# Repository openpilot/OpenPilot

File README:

This branch holds utilities to maintain the git repository

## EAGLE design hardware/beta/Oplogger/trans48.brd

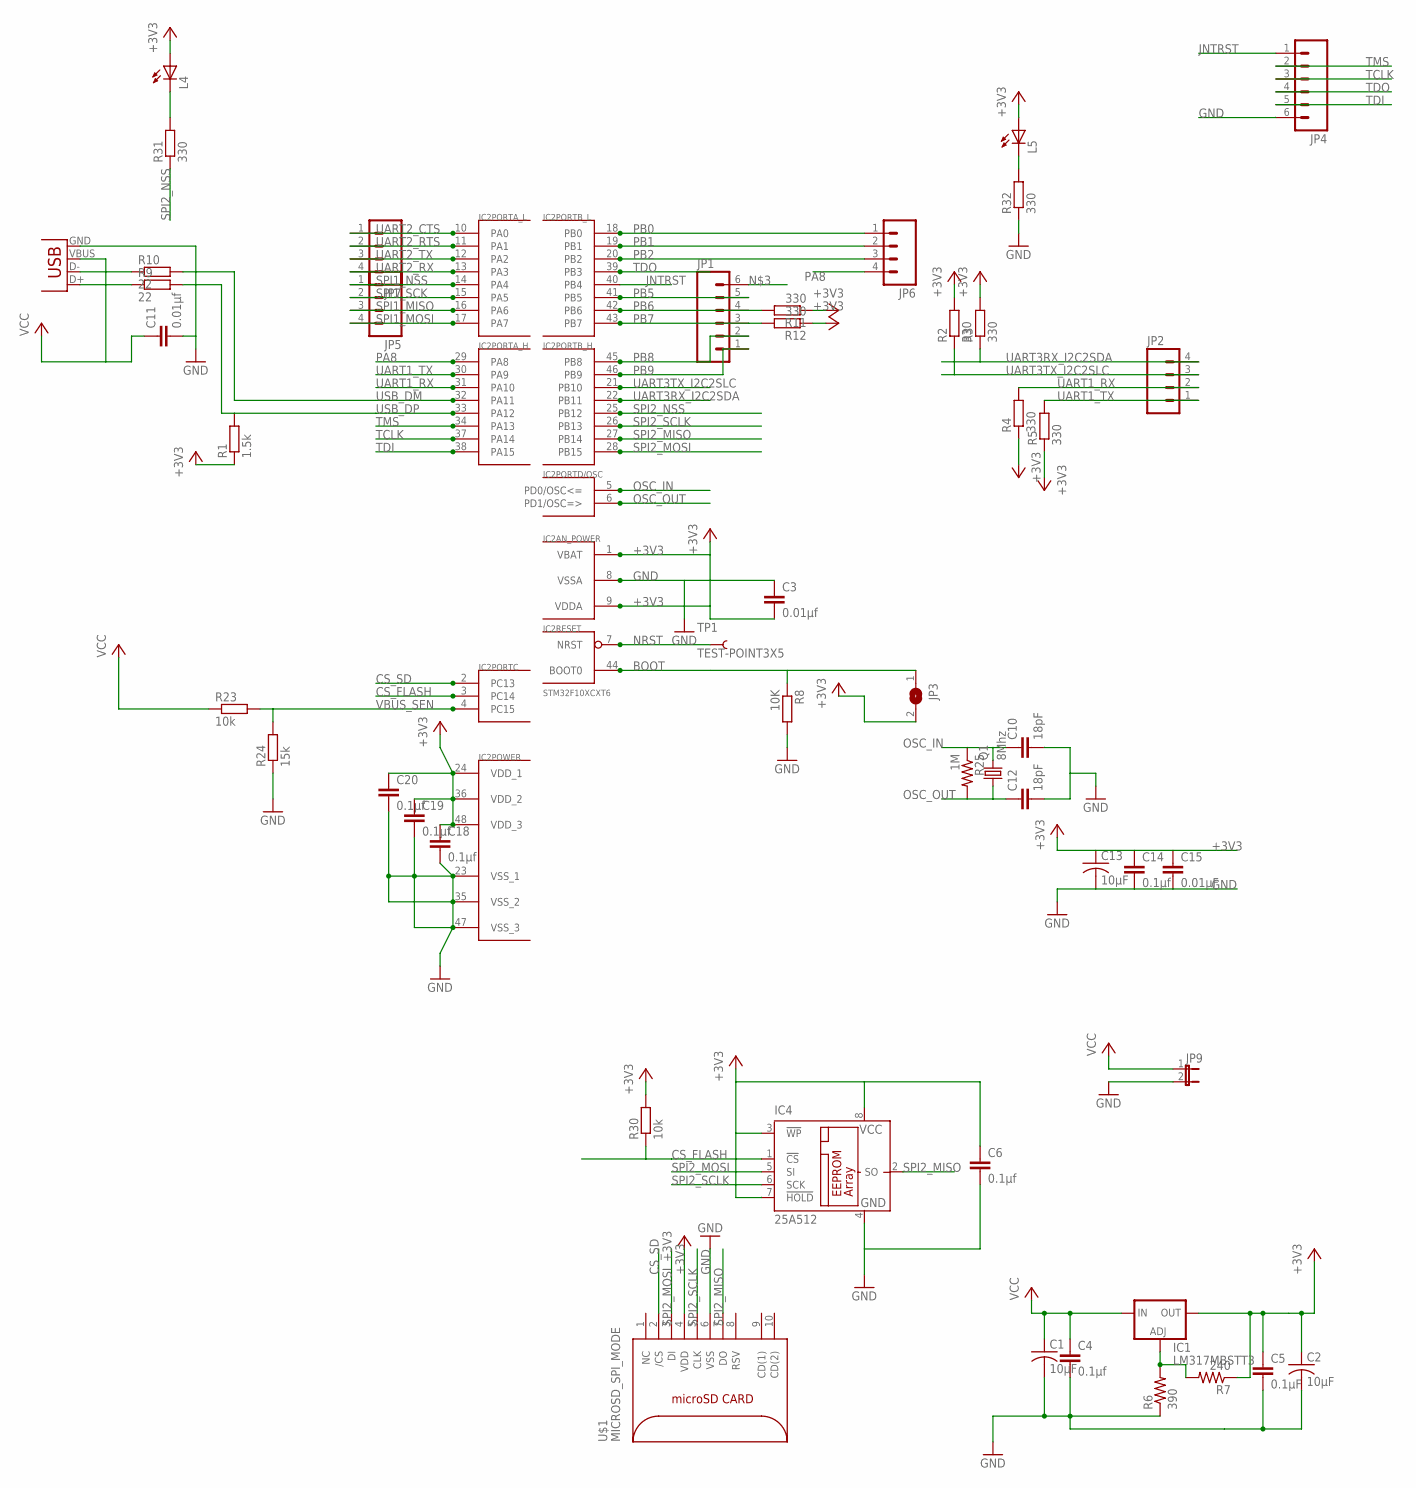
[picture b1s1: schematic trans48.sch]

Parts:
C1, C2, C13: 10µF; C1206
C3, C11: 0.01µf; C0402
C4, C6, C18, C19, C20: 0.1µf; C0402
C5: 0.1µF; C0402
C10, C12: 18pF; C0603
C14: 0.1µf; C0603
C15: 0.01µF; C0603
IC1: LM317MBSTT3; SOT223
IC2: STM32F10XCXT6; TQFP48
IC4: 25A512; SO-08
JP1, JP4: M06EM406; EM406
JP2, JP5, JP6, JP7: M04SMD2; 1X04-1MM-RA
JP3: SJ
JP9: JUMPER-2SMD-NO-NS; SJ_2S-NO-NS
L4, L5: LEDSML0603; SML0603
Q1: 8Mhz; SM49
R1: 1.5k; R0402
R2, R3, R4, R5, R11, R12, R31, R32: 330; R0402
R6: 390; R0603
R7: 240; R0603
R8: 10K; R0402
R9, R10: 22; R0402
R23, R30: 10k; R0402
R24: 15k; R0402
R25: 1M; R0603
TP1: TEST-POINT3X5; PAD.03X.05
U$1: MICROSD_SPI_MODE; MICRO_SD_CONNECTOR
X1: USB-MICROB

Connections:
+3V3: C2.1, C3.2, C5.1, C6.1, C13.1, C14.1, C15.1, C18.1, C19.1, C20.1, IC1.4 (OUT), IC2.1 (VBAT), IC2.9 (VDDA), IC2.24 (VDD_1), IC2.36 (VDD_2), IC2.48 (VDD_3), IC4.3 (!WP), IC4.7 (!HOLD), IC4.8 (VCC), JP3.2, L4.A, L5.A, R1.1, R2.2, R3.2, R4.1, R5.1, R7.1, R11.1, R12.1, R30.2, U$1.4 (VDD)
BOOT: IC2.44 (BOOT0), JP3.1, R8.1
CS_FLASH: IC2.3 (PC14), IC4.1 (!CS), R30.1
CS_SD: IC2.2 (PC13), U$1.2 (/CS)
GND: C1.2, C2.2, C3.1, C4.2, C5.2, C6.2, C10.2, C11.2, C12.2, C13.2, C14.2, C15.2, C18.2, C19.2, C20.2, IC2.8 (VSSA), IC2.23 (VSS_1), IC2.35 (VSS_2), IC2.47 (VSS_3), IC4.4 (GND), JP4.6, JP9.2, R6.1, R8.2, R24.1, R32.1, U$1.6 (VSS), X1.GND
JNTRST: IC2.40 (PB4), JP4.1
unnamed: R10.1, X1.D-
unnamed: R9.1, X1.D+
unnamed: L4.C, R31.2
unnamed: L5.C, R32.2
unnamed: IC1.1 (ADJ), R6.2, R7.2
NRST: IC2.7 (NRST), TP1.P$1
OSC_IN: C10.1, IC2.5 (PD0/OSC<=), Q1.2, R25.1
OSC_OUT: C12.1, IC2.6 (PD1/OSC=>), Q1.1, R25.2
PA8: IC2.29 (PA8), JP6.4
PB0: IC2.18 (PB0), JP6.1
PB1: IC2.19 (PB1), JP6.2
PB2: IC2.20 (PB2), JP6.3
PB5: IC2.41 (PB5), JP1.5
PB6: IC2.42 (PB6), JP1.4, R11.2
PB7: IC2.43 (PB7), JP1.3, R12.2
PB8: IC2.45 (PB8), JP1.2
PB9: IC2.46 (PB9), JP1.1
SPI1_MISO: IC2.16 (PA6), JP5.3
SPI1_MOSI: IC2.17 (PA7), JP5.4
SPI1_NSS: IC2.14 (PA4), JP5.1
SPI1_SCK: IC2.15 (PA5), JP5.2
SPI2_MISO: IC2.27 (PB14), IC4.2 (SO), U$1.7 (DO)
SPI2_MOSI: IC2.28 (PB15), IC4.5 (SI), U$1.3 (DI)
SPI2_NSS: IC2.25 (PB12), R31.1
SPI2_SCLK: IC2.26 (PB13), IC4.6 (SCK), U$1.5 (CLK)
TCLK: IC2.37 (PA14), JP4.3
TDI: IC2.38 (PA15), JP4.5
TDO: IC2.39 (PB3), JP4.4
TMS: IC2.34 (PA13), JP4.2
UART1_RX: IC2.31 (PA10), JP2.2, R4.2
UART1_TX: IC2.30 (PA9), JP2.1, R5.2
UART2_CTS: IC2.10 (PA0), JP7.1
UART2_RTS: IC2.11 (PA1), JP7.2
UART2_RX: IC2.13 (PA3), JP7.4
UART2_TX: IC2.12 (PA2), JP7.3
UART3RX_I2C2SDA: IC2.22 (PB11), JP2.4, R3.1
UART3TX_I2C2SLC: IC2.21 (PB10), JP2.3, R2.1
USB_DM: IC2.32 (PA11), R10.2
USB_DP: IC2.33 (PA12), R1.2, R9.2
VBUS_SEN: IC2.4 (PC15), R23.2, R24.2
VCC: C1.1, C4.1, C11.1, IC1.3 (IN), JP9.1, R23.1, X1.VBUS

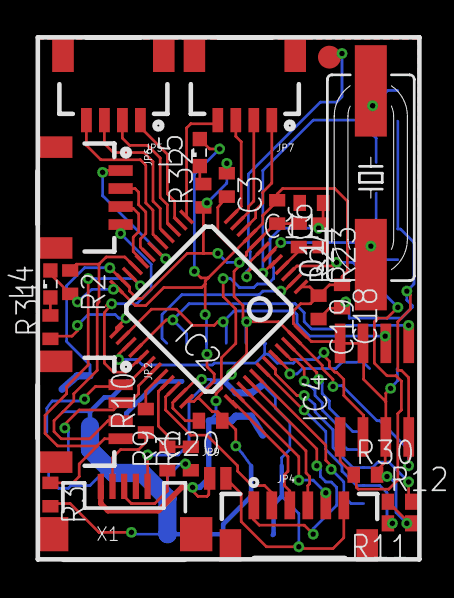
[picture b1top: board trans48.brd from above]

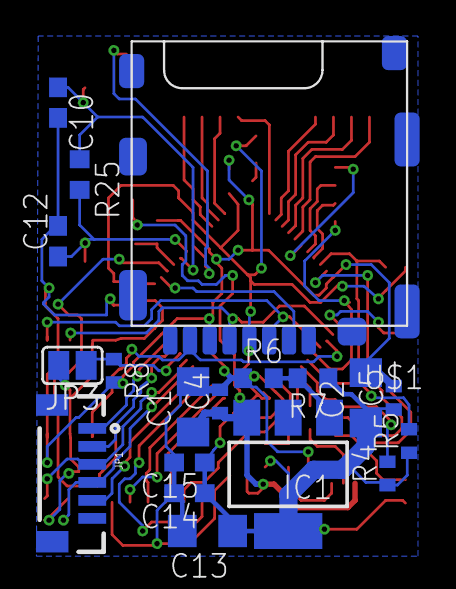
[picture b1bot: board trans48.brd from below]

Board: 2 copper layers, 50 parts (19 on the bottom side), 47 nets.

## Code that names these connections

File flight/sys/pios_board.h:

/**
 ******************************************************************************
 *
 * @file       pios_board.h   
 * @author     The OpenPilot Team, http://www.openpilot.org Copyright (C) 2009.   
 * @brief      Defines board hardware for the OpenPilot Version 0.1 hardware.
 * @see        The GNU Public License (GPL) Version 3
 *
 *****************************************************************************/
/* 
 * This program is free software; you can redistribute it and/or modify 
 * it under the terms of the GNU General Public License as published by 
 * the Free Software Foundation; either version 3 of the License, or 
 * (at your option) any later version.
 * 
 * This program is distributed in the hope that it will be useful, but 
 * WITHOUT ANY WARRANTY; without even the implied warranty of MERCHANTABILITY 
 * or FITNESS FOR A PARTICULAR PURPOSE. See the GNU General Public License 
 * for more details.
 * 
 * You should have received a copy of the GNU General Public License along 
 * with this program; if not, write to the Free Software Foundation, Inc., 
 * 59 Temple Place, Suite 330, Boston, MA 02111-1307 USA
 */


#ifndef PIOS_BOARD_H
#define PIOS_BOARD_H

//------------------------
// Default File Settings
//------------------------
#define SETTINGS_FILE			"Settings.ini"

//------------------------
// DMA Channels Used
//------------------------
/* Channel 1  - 			*/
/* Channel 2  - SPI1 (SPI_SD_RX)	*/
/* Channel 3  - SPI1 (SPI_SD_TX)	*/
/* Channel 4  - 			*/
/* Channel 5  - 			*/
/* Channel 6  - 			*/
/* Channel 7  - 			*/
/* Channel 8  - 			*/
/* Channel 9  - 			*/
/* Channel 10 - 			*/
/* Channel 11 - 			*/
/* Channel 12 - 			*/

//------------------------
// Leds Definition   
//------------------------
#define LED1_GPIO_PORT			GPIOC
#define LED1_GPIO_PIN			GPIO_Pin_12
#define LED1_GPIO_CLK			RCC_APB2Periph_GPIOC
#define LED2_GPIO_PORT			GPIOC
#define LED2_GPIO_PIN			GPIO_Pin_13
#define LED2_GPIO_CLK			RCC_APB2Periph_GPIOC
#define NUM_LED				2

//------------------------
// I2C   
//------------------------
#define I2C_GPIO_PORT			GPIOB
#define I2C_SDA_PIN			GPIO_Pin_11
#define I2C_SCL_PIN			GPIO_Pin_10

//------------------------
// Onboard Pressure sensor   
//------------------------
#define HP03D_XCLR_GPIO_PORT		GPIOC
#define HP03D_XCLR_GPIO_PIN		GPIO_Pin_15
#define HP03D_MCLK_GPIO_PORT		GPIOA
#define HP03D_MCLK_GPIO_PIN		GPIO_Pin_1

//-------------------------
// GPS UART 
//-------------------------
#define GPS_UART			USART2
#define GPS_BAUD			57600
#define GPS_GPIO_PORT			GPIOA
#define GPS_RX_PIN			GPIO_Pin_3
#define GPS_TX_PIN			GPIO_Pin_2
#define GPS_REMAP_FUNC			{ }
#define GPS_IRQ_CHANNEL			USART2_IRQn
#define GPS_IRQHANDLER_FUNC		void USART2_IRQHandler(void)
#define GPS_CLK_FUNC			RCC_APB1PeriphClockCmd(RCC_APB1Periph_USART2, ENABLE)
#define GPS_NVIC_PRIO			IRQ_PRIO_HIGHEST

//-------------------------
// Telemetry radio UART 
//-------------------------
#define TELEM_UART        		USART3
#define TELEM_BAUD         		115200
#define TELEM_GPIO_PORT         	GPIOC
#define TELEM_RX_PIN      		GPIO_Pin_11
#define TELEM_TX_PIN      		GPIO_Pin_10
#define TELEM_REMAP_FUNC		{ GPIO_PinRemapConfig(GPIO_PartialRemap_USART3, ENABLE); }
#define TELEM_IRQ_CHANNEL		USART3_IRQn
#define TELEM_IRQHANDLER_FUNC		void USART3_IRQHandler(void)
#define TELEM_CLK_FUNC			RCC_APB1PeriphClockCmd(RCC_APB1Periph_USART3, ENABLE)
#define TELEM_NVIC_PRIO			IRQ_PRIO_HIGHEST

//-------------------------
// AUXSER USART (available instead of RX5/RX6)
//-------------------------
#define AUX_UART_BAUD			19200
#define AUX_UART_UART			USART1
#define AUX_UART_GPIO_PORT		GPIOA
#define AUX_UART_RX_PIN			GPIO_Pin_10
#define AUX_UART_TX_PIN			GPIO_Pin_9
#define AUX_UART_REMAP_FUNC		{ }
#define AUX_UART_IRQ_CHANNEL		USART1_IRQn
#define AUX_UART_IRQHANDLER_FUNC	void USART1_IRQHandler(void)
#define AUX_UART_CLK_FUNC		RCC_APB2PeriphClockCmd(RCC_APB2Periph_USART1, ENABLE)
#define AUX_UART_NVIC_PRIO		IRQ_PRIO_HIGH

//-------------------------
// USART Serial Ports
//-------------------------
#define UART_NUM			3
#define UART_RX_BUFFER_SIZE		128
#define UART_TX_BUFFER_SIZE		128

//-------------------------
// Receiver PWM inputs   
//-------------------------
#define RECEIVER1_GPIO_PORT		GPIOB
#define RECEIVER1_PIN			GPIO_Pin_2      // PB2
#define RECEIVER1_TIM_PORT		TIM3
#define RECEIVER1_CH			TIM_Channel_3   // TIM3_CH3
#define RECEIVER2_GPIO_PORT		GPIOB
#define RECEIVER2_PIN			GPIO_Pin_1      // PB1
#define RECEIVER2_TIM_PORT		TIM3
#define RECEIVER2_CH			TIM_Channel_4   // TIM3_CH4
#define RECEIVER3_GPIO_PORT		GPIOA
#define RECEIVER3_PIN			GPIO_Pin_8      // PA8
#define RECEIVER3_TIM_PORT		TIM1
#define RECEIVER3_CH			TIM_Channel_1   // TIM1_CH1
#define RECEIVER4_GPIO_PORT		GPIOA
#define RECEIVER4_PIN			GPIO_Pin_0      // PA0
#define RECEIVER4_TIM_PORT		TIM5
#define RECEIVER4_CH			TIM_Channel_1   // TIM5_CH1
#define RECEIVER5_GPIO_PORT		GPIOA
#define RECEIVER5_PIN			GPIO_Pin_10     // PA10
#define RECEIVER5_TIM_PORT		TIM1
#define RECEIVER5_CH			TIM_Channel_3   // TIM1_CH3
#define RECEIVER6_GPIO_PORT		GPIOA
#define RECEIVER6_PIN			GPIO_Pin_9      // PA9
#define RECEIVER6_TIM_PORT		TIM1
#define RECEIVER6_CH			TIM_Channel_2   // TIM1_CH2

/* Not used in v0.1 HW
#define RECEIVER7_GPIO_PORT		GPIOB
#define RECEIVER7_PIN			GPIO_Pin_4      // PB4
#define RECEIVER7_TIM_PORT		TIM3
#define RECEIVER7_CH			TIM_Channel_1   // TIM3_CH1
#define RECEIVER8_GPIO_PORT		GPIOB
#define RECEIVER8_PIN			GPIO_Pin_5      // PB5
#define RECEIVER8_TIM_PORT		TIM3
#define RECEIVER8_CH			TIM_Channel_2   // TIM3_CH2
*/

#define NUM_RECEIVER_INPUTS		6

//-------------------------
// Servo outputs   
//-------------------------
#define SERVO1_4_PORT			GPIOB
#define SERVO1_PIN			GPIO_Pin_6
#define SERVO2_PIN			GPIO_Pin_7
#define SERVO3_PIN			GPIO_Pin_8
#define SERVO4_PIN			GPIO_Pin_9
#define SERVO5_8_PORT			GPIOC
#define SERVO5_PIN			GPIO_Pin_6
#define SERVO6_PIN			GPIO_Pin_7
#define SERVO7_PIN			GPIO_Pin_8
#define SERVO8_PIN			GPIO_Pin_9

#define NUM_SERVO_OUTPUTS		8

//-------------------------
// Leveler (analog inputs)
//-------------------------
#define LEVELER_GPIO_PORT		GPIOC  
#define LEVELER_Z_PIN			GPIO_Pin_0	// ADC123_IN10
#define LEVELER_A_PIN			GPIO_Pin_1	// ADC123_IN11
#define LEVELER_B_PIN			GPIO_Pin_2	// ADC123_IN12

//-------------------------  
// USB
//-------------------------
#define USB_ACC_GPIO_PORT		GPIOC
#define USB_DETECT_PIN			GPIO_Pin_4
#define USB_PULLUP_PIN			GPIO_Pin_14

//-------------------------
// Master Clock   
//-------------------------
#define MASTER_CLOCK			72000000
#define PERIPHERAL_CLOCK		(MASTER_CLOCK/2)

//-------------------------
// Interrupt Priorities
//-------------------------
#define IRQ_PRIO_LOW			12		// lower than RTOS
#define IRQ_PRIO_MID			8		// higher than RTOS
#define IRQ_PRIO_HIGH			5		// for like SPI, AIN, I2C etc...
#define IRQ_PRIO_HIGHEST		4 		// for UART etc...

#endif /* PIOS_BOARD_H */

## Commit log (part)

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2015-04-22 OP-1843 Makefile bugs: split qmake CONFIG variables as a temporary solution to broken qmake quoting on windows
2015-04-23 OP-1806 version info escape strings for C. Added option "--escape" which uses json.dumps to do escaping
2015-04-23 OP-1848 altvari0
    1. build fixes
    2. Updated ui to use updated uavo names in altitude settings that align to the naming in vtol settings
    3. Moved call the thrust altvario to pre application of PIDs for 3d axes to allow for later coupling.
2015-04-23 OP-1838 altvario
    Fixes and tidyup.
    TODO:
    1. Fix UI for sliders
    2. Disable vtol tuning on stabi input
    3. Altitude loss feedback
2015-04-23 OP-1837 Moved to Flexiport. Updated some decoding code.
2015-04-24 OP-1848 altvario
    UI scaling fixes and help text edits.
2015-04-24 OP-1837 Renaming of perf counter.
2015-04-24 OP-1855 changed , to :
2015-04-24 OP-1849 Initial commit
2015-04-25 Add Revo hardware files
2015-04-26 OP-1849 Hooks all in place for CDC line state changes to drive port GPIO for DTR
2015-04-26 Added new helper macros to performance counters.
2015-04-26 OP-1337 Translations : input wizard update
2015-04-26 OP-1849 Uncrustify
2015-04-26 OP-1837 Fixed a wrongly named config.
2015-04-27 OP-1751 Modify some improper CN translations
2015-04-27 OP-1858 autotakeoff in pathplanner
    1. Allowing arming in pathplanner
    2. Takeoff activation requires throttle to be above 30%
    3. Takeoff occurs at the current/actual position and rises vertical to the settings altititude.
    4. The details of the takeoff waypoint are effectively ignored - this is a simplicifcation to avoid having to have pathplanner inject a flyvector command from the current location to the waypoint
    5. We hard code the condition check for autotakeoff as only one mode is supported.
2015-04-27 X-Plane 10 HITL & SITL protocol changes that should have been in place long ago!
2015-04-28 OP-1858 autotakeoff and pathplanner
    1. Allow arming in pathplanner
    2. Typo in comment
2015-04-28 OP-1835 - Next Motor Constraints - Diff Addition Method
    Using the Difference / Addition method to compare it against the
    multiplication method.
2015-04-28 Fix some minor issues with the old Wireshark Plugin. It won't compile past Wireshark 1.8 which is way outdated. added void *data _U_ to the dissecor definition per - https://ask.wireshark.org/questio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
2015-04-28 Fix the error "Err Field '0' (actuatorcommand.Channel.0) is signed (FT_INT16) but is being displayed unsigned (BASE_DEC_HEX)" Stop attempting to display in hex
2015-04-28 Fix WhatsNew for release
2015-04-29 OP-1835 - Master Motor Constraints - Flow changes
2015-04-30 OP-1840 CC3D wouldn't build and update some comments
2015-04-30 resurrect missing / deleted pyuavtalk files & examples. Work with Viper to bring back up to date with current codebase.
2015-04-30 Fix the python file read example to properly read the filename from commandline. Adjusted argv accordingly in python code.
2015-05-01 Add uavobjects_python_clean function to remove the UAVOs, reduce likely hood of stale files being used.
2015-05-01 fix uavobject paths
2015-05-01 OP-1840 Remove reference to unreleased hardware
2015-05-01 OP-1870 Velocity Roam
    Auto yaw if vtolpathfollowersettings.YawControl is set to MovementDirection.
    1. Fast-forward pitch with slight roll will slowly introduce yaw continuosly, which also continuosly introduces additional banking of velocities in the NE directions, forming a circle of a large radi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
    2. Zero forward pitch, with just roll input, will trigger yaw rate quickly approaching max yaw rate, which may need to be reduced.
2015-05-01 OP-1835 - Master Motor Constraints - Bugfix
    Incorrect if/then statement
2015-05-02 OP-802 adapted gstreamer copydata.pro to use new addCopyFileTarget macro (thanks James!)
2015-05-02 OP-802 stop pipeline on error
2015-05-02 OP-802 added more plugins
2015-05-02 uncrustified
2015-05-02 OP-1835 - Motor Constraints for 15.02.02 - Quick fix to disable clipping. Bit of code not in the original fix I had to deal with.
2015-05-02 OP-1835 - Motor Constraints 15.02.02 100% throttle curves default
2015-05-03 OP-1873 - Uncrustify - Non Inverted Sbus for Flight Testing.
2015-05-03 Update WHATSNEW.txt - rel-15.02.02-RC3
2015-05-03 OP-1873 - Fix Compile Errors
2015-05-03 OP-1847 altvario update of tuning parameters for piddown control
2015-05-04 OP-1863 ratetrainer fix coding error. ratetrainer should now work.
2015-05-05 OP-187- velocityroam auto-yaw
    uncrustify
2015-05-05 OP-1848 build fixes after merge with ratetrainer
2015-05-05 OP-1848 altvario Update dT to speed on sensor update rate
2015-05-05 Be mindful of linux users not using brew on OSX... should be using sudo (not running make as root)
2015-05-06 Fix the serial connection in example.py
2015-05-06 OP-1840 another merge conflict
2015-05-06 Make changes to example python code so it makes use of StabilizationSettingsBank1 Fix some printf() errors on the tuple that held PID settings... needed one more field Fix Keyboard interrupt on one e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
2015-05-07 Don't need to request all the data first, just start read.
2015-05-07 Pull request from user aughey on github - https://github.com/openpilot/OpenPilot/pull/4/files
    Covers commits:
    This is noisy, but does talk to the CC3D - c59543a
    Don't need to request all the data first, just start read. - e4df881
    Printing RPY for testing - e3117df
2015-05-07 OP-1873 - Non Inverted S.Bus support. Based off Next.
2015-05-07 OP-1810 FOC GCS
2015-05-08 OP-1803 Disable untested DSM link quality code
2015-05-08 OP-1810 FOC re-add back in removed case statement
2015-05-08 OP-1858 takeoff in nav address code review comments
2015-05-09 OP-1848 altvario discovery4bare remove second instance of uavo
2015-05-09 Upgrade HK CCs
2015-05-09 OP-1831 - Update Ki Limits
2015-05-10 OP-1853 Ground build tidy: remove unneeded line in translations.pro
2015-05-10 OP-1810-FOC review comments
2015-05-10 Add search coloring back to the location search. Google Maps should be functional again. Some locations on the extents of map do not render 'North Pole, South Pole, Antarctica, etc.' currently a *non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
2015-05-10 OP-1810-FOCv2 undoing usb driver changes
2015-05-11 OP-1810 CC/CC3D message box : Change text and icon
2015-05-11 OP-1810 usagetracker : remove CC
2015-05-12 OP-1848 altvario fixes
    1. CC compile fix
    2. on reinit calculate a new thrustdemand after which gyro updates will retrigger subsequent calcs
2015-05-12 OP-1848 altvario gcs fix ranges
2015-05-13 OP-1810-FOC uncrustify
2015-05-13 uncrustify flight gps updates
2015-05-13 OP-1853 Ground build tidy: Remove old android line
2015-05-13 OP-1853 Ground build tidy: Make UAVO_BUILD_CONF use GCS_BUILD_CONF to match qtcreator builds and make things easier later
2015-05-13 OP-1853 Ground build tidy: removed now unneeded uavobject-synthetics.pro
2015-05-13 Fix SigPacSpainMap & Google*Korea map types
2015-05-13 OP-1869 "scale" lower case
2015-05-13 OP-1887 Hide battery links when battery panel not displayed
2015-05-14 OP-1887 Missing file for tooltips
2015-05-14 attempt to get Pergo Turkish maps working. Still buggy. Unable to search and auto zoom. Initial map render works mostly
2015-05-14 OP-1847 gps assist fixes
    1. Update vtol vertical pids
    2. Reduce deadband on throttle in gpsassist auto throttle to avoid large deviations in throttle change from neutral
    3. Reinitialise assisted control state on mode change where the flight is the same but only gpsassist is going from disabled to enabled or enabled to disabled.
2015-05-14 OP-1887 Add Receiver quality
2015-05-14 OP-1887 Oups, QuadH resurrected...
2015-05-15 OP-1337 Translations updates for rel-15.05
2015-05-15 Depreciate Yandex maps
2015-05-16 OP-1847 gpsassist fix
    Set assisted control state to HOLD when Brake controller transitions to HOLD. This impacts throttle stick behavior as it is different during braking and on brake completion in the hold state.
    Also cleanuped and removed unused/old code that triggered HOLD in plans.c
2015-05-16 OP-1882 set thrust control to auto as default
2015-05-17 Fixing indent spacing for OC reasons.
2015-05-17 adding a size output for json
2015-05-17 Add code from John Aughey - jha@aughey.com https://github.com/aughey/OpenPilot/commit/95726c7cf3f909e24c5cc5e8cd3ece56a564dff1?diff=unified
2015-05-17 add json bits to the generator
2015-05-17 OP-1892 Convert / Add descriptions
2015-05-17 change Json path to be relative to the project root. Files should be present after: make uavtalk_json; ls build/uavobject-synthetics/json
2015-05-17 add more examples to the README file. fix the serial example to be more robust
2015-05-17 OP-1893 Apply scale to reach +1/-1 range
2015-05-17 This closes https://progress.openpilot.org/browse/OP-1888
2015-05-18 OP-1892 Formatting, second round
2015-05-18 OP-1464 GPS autobaud - stash while debugging newobject issue
2015-05-19 OP-1854 Allow EKF reset with mouseclick on PFD alarm
2015-05-19 15.05 Update contributors
2015-05-20 OP-1464 remove commented out or unused code and pretty it up
2015-05-20 OP-1464 Compile warning discovery Remove AbConfStoreDisable
2015-05-21 OP-1897 Minor change after code review
2015-05-21 OP-1888: Fix SEGFAULT when deleting config.
2015-05-23 OP-1879 remove openpilot hardcoding: use same app target on all platforms
2015-05-23 OP-1879 remove openpilot hardcoding: remove udp_test from Linux install like other platforms
2015-05-23 OP-1879 remove openpilot hardcoding: change GCS_APP_PATH on Mac removing pointless bin subdir
2015-05-23 OP-1879 remove openpilot hardcoding: remove unused hardcoded cloudconfig path
2015-05-23 OP-1879 remove openpilot hardcoding: reworked settings to use default app name
2015-05-23 OP-1879 remove openpilot hardcoding: use $$shell_quote where appropraite
2015-05-23 OP-1695 Ubuntu PPA: actually put debs in PACKAGE_DIR
2015-05-23 OP-1695 Ubuntu PPA: made OP modifications in package rule rather than hardcoded to debian rules file
2015-05-23 OP-1695 Ubuntu PPA: made .gz a make target
2015-05-23 OP-1695 Ubuntu PPA: made debian/rules executable
2015-05-23 OP-1695 Ubuntu PPA: update standards version and deb builder version
2015-05-23 OP-1695 Ubuntu PPA: made dist targets depend on .git/index instead of being PHONY
2015-05-23 OP-1695 Ubuntu PPA: set debian section to electronics
2015-05-23 OP-1695 Ubuntu PPA: added trusty depends workaround
2015-05-23 OP-1695 Ubuntu PPA: remove dirty from version-info.json
2015-05-23 OP-1695 Ubuntu PPA: suppress 'which' stderr
2015-05-23 OP-1790: remove debain rules hack and build package without clean
2015-05-23 OP-1790: make packaging debug build error part of package rule
2015-05-23 OP-1792: make firmware_info.c depend on uavobjectdefition instead of FORCE so it isn't always updated
2015-05-23 OP-1700 copydata doubles if called twice: reused code for all platforms. Note this may make mixed case directories on windows
2015-05-23 OP-1792 makefile tidy: removed unneeded quotes for OPENSSL that break copydata makefile
2015-05-23 OP-1792 Makefile tidy: Create a rule for all directories in Makefile
2015-05-23 OP-1667 removed old firmware line from windows package
2015-05-23 OP-1851 Missing static keyword:
    Added static to header functions that were missing it
2015-05-23 OP-1900 New settings for autotakeoff/autoland added
2015-05-23 OP-1900 manual induced autotakeoff sequencing safer for multis and fixed wing
2015-05-23 OP-1879 remove openpilot hardcoding: update Darwin packaging to use make GCS_X_NAME variables
2015-05-23 OP-1901 Add Multiplex SRXL artwork
2015-05-23 fix flightgear hitl bridge sign issue on velocity down vector
2015-05-24 OP-1879 remove openpilot hardcoding: update Windows packaging to use make GCS_X_NAME variables
2015-05-24 OP-1879 Remove openpilot hardcoding: make debian package use OP name variables
2015-05-25 rename to OpenPilot TEST
2015-05-30 OP-1911 Add avr_sdk_install target for OS X
2015-05-30 OP-1911 Undo unintended line merge
2015-05-30 OP-1911 Define common root URLs for AVR
2015-06-01 remove unused lines in file example
2015-06-01 Skip the AccelGyroSettings UAVO, as it is not properly parsing. File parser now works. Adjust timing of parse thread, increase pause to allow for UAVO .json files to be injested.
2015-06-04 OP-1900 get rid of highpower error by default again (too many false positives)
2015-06-04 OP-1900 have path_progress updated correctly for leg_remaining and error_below end conditions to work in fixedwingautotakeoff
2015-06-04 OP-1886 smarter sdk_install target: rework file download targets

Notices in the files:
parts and their libraries:
SparkFun: Licensing: CC v3.0 Share-Alike You are welcome to use this library for commercial purposes.
